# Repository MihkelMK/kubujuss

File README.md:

# kubujuss WIP
This is my second custom keyboard. I started with a Keychron K2 with lubed Gateron Yellows and a custom slimmer case without the battery. It has served me well but the barrage of keyboard content has slowly built up the urge to make another one.

Typically there seems to be some keyboard inbetween a 75% layout and minimal split keyboard, but the soothing and dangerously approachable videos of Ben Wallok have radicalised me beyond repair.

## So here we are
34 keys split into 2 seperate halves.

Column stagger was adjusted by eye to match some illustrations and mockups I made on paper.

I found the pinkie cluster idea on accient, when I tried to find images of split keyboards on google. I found an image of [Wubbo](https://github.com/cacheworks/Wubbo). It seemed weird at first but the first tests on paper seemed promising. Time will tell if it works in real life as well.

## Thanks
Big thanks for [FlatFootFox](https://flatfootfox.com/) for his awesome [introduction to ergogen v4](https://flatfootfox.com/ergogen-introduction/). This guide taught me everything I know about ergogen and kicad.

And a gigantic thanks for @christianselig, for helping me figure out how to make both PCB halves in one ergogen file.

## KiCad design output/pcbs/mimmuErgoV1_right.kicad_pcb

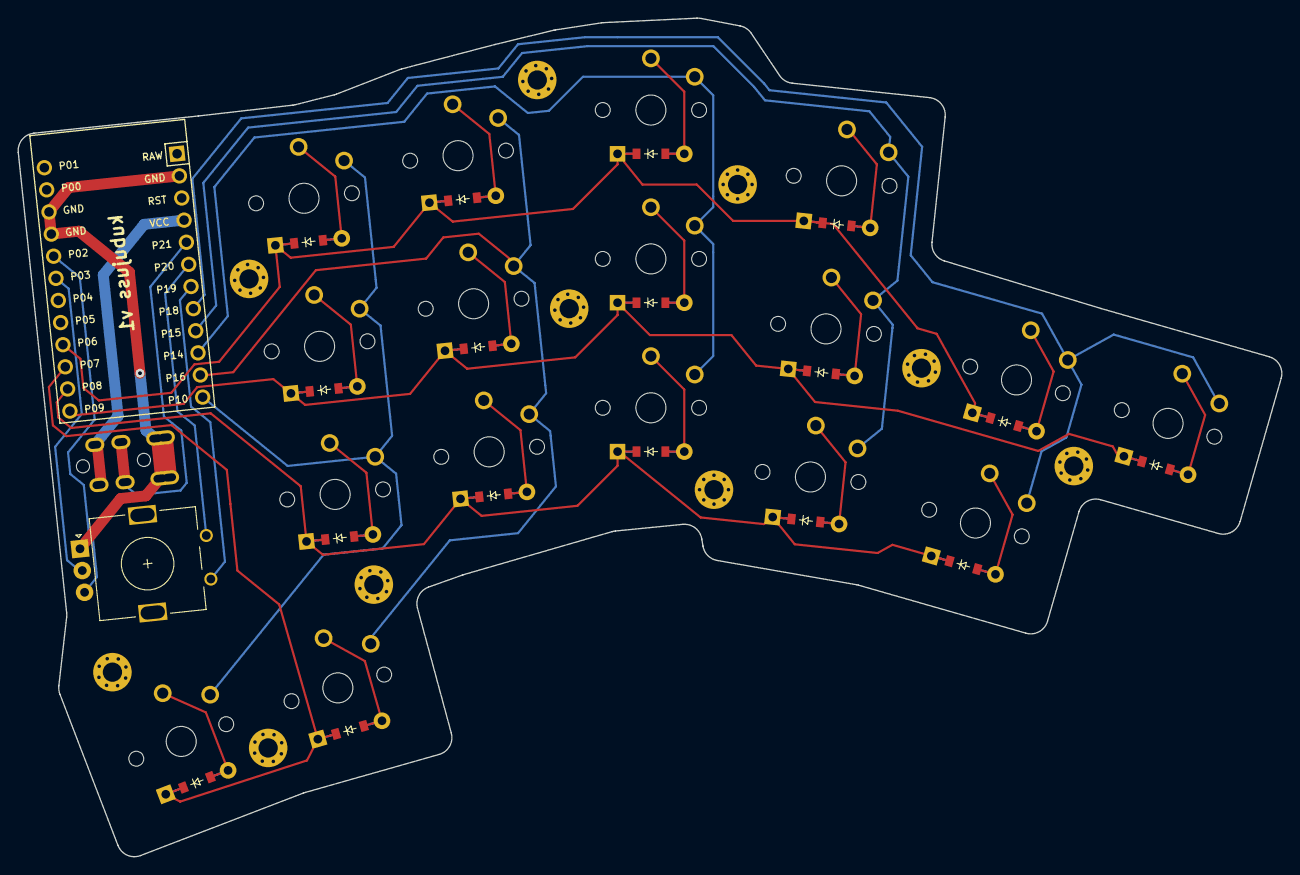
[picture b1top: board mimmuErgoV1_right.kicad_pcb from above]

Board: 2 copper layers, 144.3 x 95.7 mm, 47 parts (0 on the bottom side), 33 nets.

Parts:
D1, D2, D3, D4, D5, D6, D7, D8, D9, D10, D11, D12, D13, D14, D15, D16, D17: ComboDiode
MCU1: ProMicro
ROT1: rotary_encoder
S1, S2, S3, S4, S5, S6, S7, S8, S9, S10, S11, S12, S13, S14, S15, S16, S17: PG1350
TRRS1: TRRS-PJ-320A-dual
_1, _2, _3, _4, _5, _6, _7, _8, _9, _10: MountingHole_2.2mm_M2_Pad_Via

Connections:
GND: MCU1.2, MCU1.15, MCU1.16, ROT1.A, TRRS1.1, TRRS1.2
P2: MCU1.17, ROT1.B
P3: MCU1.18, ROT1.C
P6: D2.1, D6.1, D9.1, D12.1, D15.1, MCU1.21
P7: D16.1, D17.1, MCU1.22
P8: D1.1, D4.1, D7.1, D10.1, D13.1, MCU1.23
P9: D3.1, D5.1, D8.1, D11.1, D14.1, MCU1.24
P10: MCU1.12, S13.1, S14.1, S15.1, S17.1
P14: MCU1.10, S7.1, S8.1, S9.1
P15: MCU1.9, S4.1, S5.1, S6.1
P16: MCU1.11, S10.1, S11.1, S12.1, S16.1
P18: MCU1.8, S1.1, S2.1, S3.1
P19: MCU1.7, ROT1.2
P20: MCU1.6, ROT1.1
P21: MCU1.5, TRRS1.3
VCC: MCU1.4, TRRS1.4
mirror_index_bottom: D10.2, S10.2
mirror_index_home: D11.2, S11.2
mirror_index_top: D12.2, S12.2
mirror_inner_bottom: D13.2, S13.2
mirror_inner_home: D14.2, S14.2
mirror_inner_top: D15.2, S15.2
mirror_layer_cluster: D16.2, S16.2
mirror_middle_bottom: D7.2, S7.2
mirror_middle_home: D8.2, S8.2
mirror_middle_top: D9.2, S9.2
mirror_pinkie_bottom: D1.2, S1.2
mirror_pinkie_home: D2.2, S2.2
mirror_pinkie_top: D3.2, S3.2
mirror_ring_bottom: D4.2, S4.2
mirror_ring_home: D5.2, S5.2
mirror_ring_top: D6.2, S6.2
mirror_space_cluster: D17.2, S17.2

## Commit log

2023-11-16 add first draft
2023-11-16 Fix link syntax
2023-11-20 finalize
2023-11-23 Make GND and VCC traces 1mm thicker
